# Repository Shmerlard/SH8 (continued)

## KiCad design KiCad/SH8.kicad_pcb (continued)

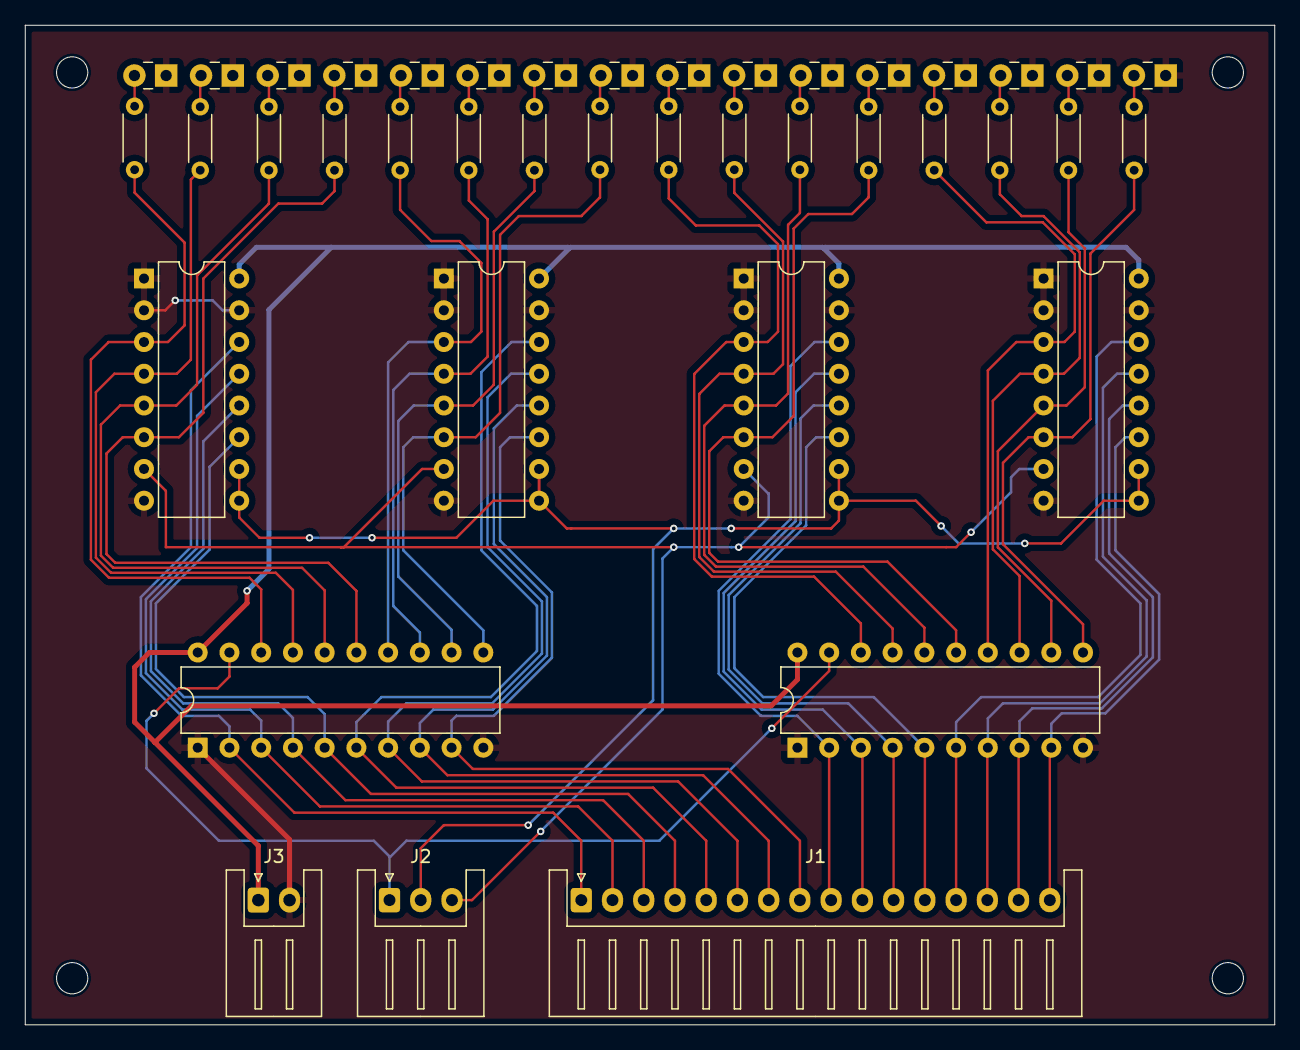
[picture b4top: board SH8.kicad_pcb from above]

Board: 2 copper layers, 100.0 x 80.0 mm, 41 parts (0 on the bottom side), 53 nets.
